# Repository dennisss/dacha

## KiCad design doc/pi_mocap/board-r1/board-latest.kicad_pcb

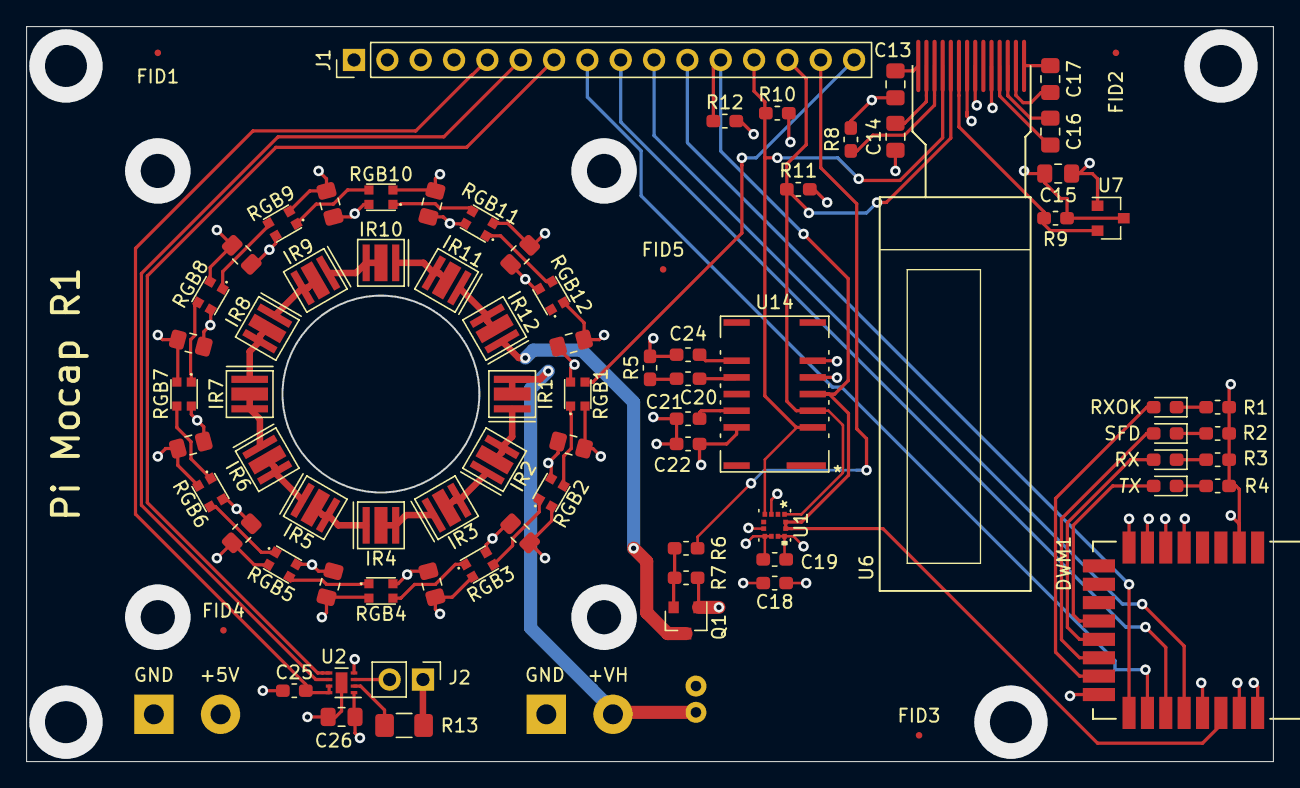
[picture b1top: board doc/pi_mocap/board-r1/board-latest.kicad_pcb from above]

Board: 4 copper layers, 95.0 x 56.0 mm, 83 parts (1 on the bottom side), 61 nets.

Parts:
C1, C2, C3, C4, C5, C6, C7, C8, C9, C10, C11, C12, C26: 0.1u; C_0805_2012Metric_Pad1.15x1.40mm_HandSolder
C13, C14, C15: 10u; C_0805_2012Metric_Pad1.15x1.40mm_HandSolder
C16, C17: 1u; C_0805_2012Metric_Pad1.15x1.40mm_HandSolder
C18, C22: 10u; C_0603_1608Metric_Pad1.05x0.95mm_HandSolder
C19: 100n; C_0603_1608Metric_Pad1.05x0.95mm_HandSolder
C20: 1u; C_0603_1608Metric_Pad1.05x0.95mm_HandSolder
C21: 1.5u; C_0603_1608Metric_Pad1.05x0.95mm_HandSolder
C23: 100u; C_Radial_D5.0mm_H11.0mm_P2.00mm
C24, C25: 0.1u; C_0603_1608Metric_Pad1.05x0.95mm_HandSolder
D1: RXOK; LED_0603_1608Metric_Pad1.05x0.95mm_HandSolder
D2: SFD; LED_0603_1608Metric_Pad1.05x0.95mm_HandSolder
D3: RX; LED_0603_1608Metric_Pad1.05x0.95mm_HandSolder
D4: TX; LED_0603_1608Metric_Pad1.05x0.95mm_HandSolder
DWM1: DWM1000
FID1, FID2, FID3, FID4, FID5: Fiducial; Fiducial_0.5mm_Mask1mm
IR1, IR2, IR3, IR4, IR5, IR6, IR7, IR8, IR9, IR10, IR11, IR12: LED; WURTH_15435385A9040
J1: AUX; PinHeader_1x16_P2.54mm_Vertical
J2: SOLENOID; PinHeader_1x02_P2.54mm_Vertical
J3: LED_DCDC_IN; TerminalBlock_bornier-2_P5.08mm
J4: LED_DCDC_OUT; TerminalBlock_bornier-2_P5.08mm
Q1: AO3422; SOT-23
R1, R2, R3, R4: 200; R_0603_1608Metric_Pad1.05x0.95mm_HandSolder
R5: 20; R_0603_1608Metric_Pad1.05x0.95mm_HandSolder
R6: 1K; R_0603_1608Metric_Pad1.05x0.95mm_HandSolder
R7, R9, R10, R11, R12: 10K; R_0603_1608Metric_Pad1.05x0.95mm_HandSolder
R8: 390K; R_0603_1608Metric_Pad1.05x0.95mm_HandSolder
R13: NC; R_1206_3216Metric_Pad1.42x1.75mm_HandSolder
RGB1, RGB2, RGB3, RGB4, RGB5, RGB6, RGB7, RGB8, RGB9, RGB10, RGB11, RGB12: WS2812B-2020
U1: LIS2DW12TR
U2: DRV8837; WSON-8-1EP_2x2mm_P0.5mm_EP0.9x1.6mm
U6: SSD1306; SSD1306_OLED-0.91-128x32
U7: APX803; SOT-23
U14: AMG8854

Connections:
+3V3: C15.2, C18.1, C19.1, C22.1, C24.1, C25.1, DWM1.5, DWM1.6, DWM1.7, J1.5, R9.2, R10.2, R11.2, R12.2, U1.9, U1.10, U2.7, U2.8, U6.5, U6.8, U7.3, U14.9, U14.13
+5V: C1.1, C2.1, C3.1, C4.1, C5.1, C6.1, C7.1, C8.1, C9.1, C10.1, C11.1, C12.1, C26.2, J1.1, J1.2, J3.2, RGB1.4, RGB2.4, RGB3.4, RGB4.4, RGB5.4, RGB6.4, RGB7.4, RGB8.4, RGB9.4, RGB10.4, RGB11.4, RGB12.4, U2.1
GND: C1.2, C2.2, C3.2, C4.2, C5.2, C6.2, C7.2, C8.2, C9.2, C10.2, C11.2, C12.2, C13.1, C14.1, C15.1, C18.2, C19.2, C21.2, C22.2, C23.2, C24.2, C25.2, C26.1, DWM1.2, DWM1.8, DWM1.16, DWM1.21, DWM1.23, DWM1.24, J1.3, J1.4, J3.1, J4.1, Q1.1, R1.2, R2.2, R3.2, R4.2, R5.2, R7.1, R8.2, RGB1.2, RGB2.2, RGB3.2, RGB4.2, RGB5.2, RGB6.2, RGB7.2, RGB8.2, RGB9.2, RGB10.2, RGB11.2, RGB12.2, U1.3, U1.6, U1.7, U1.8, U2.4, U2.9, U6.7, U7.1, U14.5, U14.6
IR_LED_PWM: J1.15, R6.1
IR_LED_VCC: C23.1, IR1.2, J4.2
LED_SERIAL: J1.16, RGB1.3
unnamed: C13.2, U6.14
unnamed: C14.2, U6.13
unnamed: C16.1, U6.4
unnamed: C16.2, U6.3
unnamed: C17.1, U6.2
unnamed: C17.2, U6.1
unnamed: C20.1, U14.10
unnamed: C20.2, R5.1
unnamed: C21.1, U14.12
unnamed: D1.1, R1.1
unnamed: D1.2, DWM1.15
unnamed: D2.1, R2.1
unnamed: D2.2, DWM1.14
unnamed: D3.1, R3.1
unnamed: D3.2, DWM1.13
unnamed: D4.1, R4.1
unnamed: D4.2, DWM1.12
unnamed: IR1.1, IR2.2
unnamed: IR2.1, IR3.2
unnamed: IR3.1, IR4.2
unnamed: IR4.1, IR5.2
unnamed: IR5.1, IR6.2
unnamed: IR6.1, IR7.2
unnamed: IR7.1, IR8.2
unnamed: IR8.1, IR9.2
unnamed: IR10.1, IR11.2
unnamed: IR9.1, IR10.2
unnamed: IR11.1, IR12.2
unnamed: IR12.1, Q1.3
unnamed: J2.1, R13.2
unnamed: J2.2, U2.3
unnamed: Q1.2, R6.2, R7.2
unnamed: R8.1, U6.12
unnamed: R13.1, U2.2
unnamed: RGB1.1, RGB2.3
unnamed: RGB2.1, RGB3.3
unnamed: RGB3.1, RGB4.3
unnamed: RGB4.1, RGB5.3
unnamed: RGB5.1, RGB6.3
unnamed: RGB6.1, RGB7.3
unnamed: RGB7.1, RGB8.3
unnamed: RGB8.1, RGB9.3
unnamed: RGB10.1, RGB11.3
unnamed: RGB9.1, RGB10.3
unnamed: RGB11.1, RGB12.3
OLED_RESET: R9.1, U6.9, U7.2
PI_I2C0_SCL: J1.14, R11.1, U1.1, U6.10, U14.3
PI_I2C0_SDA: J1.13, R10.1, U1.4, U6.11, U14.2
PI_SPI0_CE0: DWM1.17, J1.11
PI_SPI0_SCLK: DWM1.20, J1.10
PI_SPIO_MISO: DWM1.19, J1.9
PI_SPIO_MOSI: DWM1.18, J1.8
SENSOR_INTERRUPT: DWM1.22, J1.12, R12.1, U1.11, U1.12, U14.4
SOLENOID_DIR1: J1.6, U2.6
SOLENOID_DIR2: J1.7, U2.5

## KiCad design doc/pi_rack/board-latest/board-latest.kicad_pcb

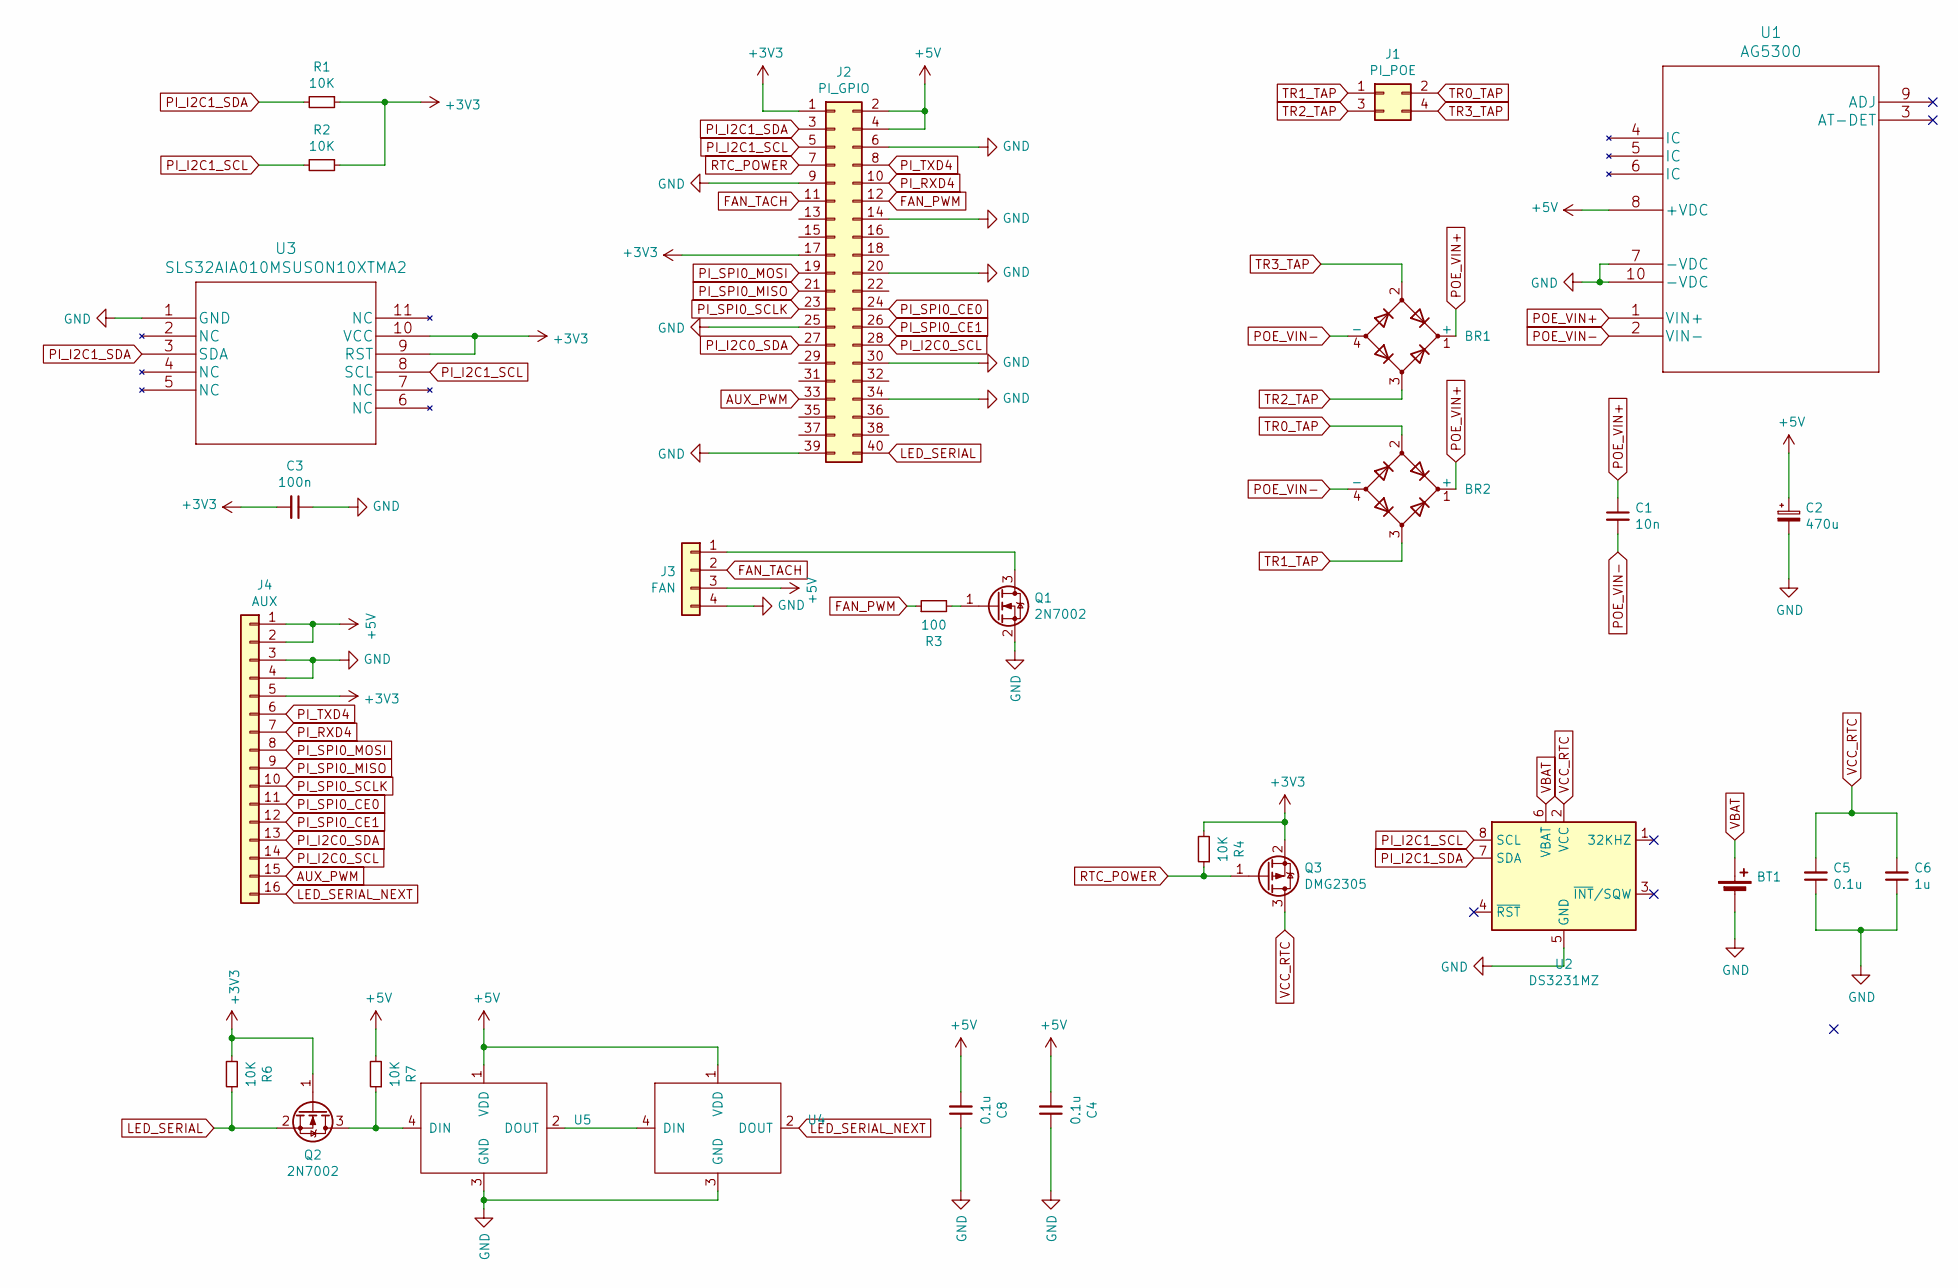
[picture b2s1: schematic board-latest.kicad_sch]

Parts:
BR1, BR2: D_Bridge_+AA-; CD-HD2004
BT1: Battery_Cell; BatteryHolder_Keystone_3000_1x12mm
C1: 10n; C_0805_2012Metric_Pad1.15x1.40mm_HandSolder
C2: 470u; CP_Radial_D10.0mm_P5.00mm
C3: 100n; C_0603_1608Metric_Pad1.05x0.95mm_HandSolder
C4, C8: 0.1u; C_0805_2012Metric_Pad1.15x1.40mm_HandSolder
C5: 0.1u; C_0603_1608Metric_Pad1.05x0.95mm_HandSolder
C6: 1u; C_0603_1608Metric_Pad1.05x0.95mm_HandSolder
J1: PI_POE; PinSocket_1x04_P2.54mm_Horizontal
J2: PI_GPIO; PinSocket_2x20_P2.54mm_Horizontal
J3: FAN; JST_SH_SM04B-SRSS-TB_1x04-1MP_P1.00mm_Horizontal
J4: AUX; Harwin_M20-89016xx_1x16_P2.54mm_Horizontal
Q1, Q2: 2N7002; SOT-23
Q3: DMG2305; SOT-23
R1, R2, R4, R6, R7: 10K; R_0603_1608Metric_Pad1.05x0.95mm_HandSolder
R3: 100; R_0603_1608Metric_Pad1.05x0.95mm_HandSolder
U1: AG5300; AG5400
U2: DS3231MZ; SOIC-8_3.9x4.9mm_P1.27mm
U3: SLS32AIA010MSUSON10XTMA2
U4, U5: SK6812MINI-E; SK6812B-SIDE

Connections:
+3V3: C3.2, J2.1, J2.17, J4.5, Q2.1 (G), Q3.2 (S), R1.1, R2.1, R4.2, R6.2, U3.9 (RST), U3.10 (VCC)
+5V: C2.1, C4.2, C8.2, J2.2, J2.4, J3.3, J4.1, J4.2, R7.2, U1.8 (+VDC), U4.1 (VDD), U5.1 (VDD)
AUX_PWM: J2.33, J4.15
FAN_PWM: J2.12, R3.1
FAN_TACH: J2.11, J3.2
GND: BT1.2 (-), C2.2, C3.1, C4.1, C5.1, C6.1, C8.1, J2.6, J2.9, J2.14, J2.20, J2.25, J2.30, J2.34, J2.39, J3.4, J4.3, J4.4, Q1.2 (S), U1.7 (-VDC), U1.10 (-VDC), U2.5 (GND), U3.1 (GND), U4.3 (GND), U5.3 (GND)
LED_SERIAL: J2.40, Q2.2 (S), R6.1
LED_SERIAL_NEXT: J4.16, U4.2 (DOUT)
unnamed: J3.1, Q1.3 (D)
unnamed: Q1.1 (G), R3.2
unnamed: Q2.3 (D), R7.1, U5.4 (DIN)
unnamed: U4.4 (DIN), U5.2 (DOUT)
PI_I2C0_SCL: J2.28, J4.14
PI_I2C0_SDA: J2.27, J4.13
PI_I2C1_SCL: J2.5, R2.2, U2.8 (SCL), U3.8 (SCL)
PI_I2C1_SDA: J2.3, R1.2, U2.7 (SDA), U3.3 (SDA)
PI_RXD4: J2.10, J4.7
PI_SPI0_CE0: J2.24, J4.11
PI_SPI0_CE1: J2.26, J4.12
PI_SPI0_MISO: J2.21, J4.9
PI_SPI0_MOSI: J2.19, J4.8
PI_SPI0_SCLK: J2.23, J4.10
PI_TXD4: J2.8, J4.6
POE_VIN+: BR1.1 (+), BR2.1 (+), C1.1, U1.1 (VIN+)
POE_VIN-: BR1.4 (-), BR2.4 (-), C1.2, U1.2 (VIN-)
RTC_POWER: J2.7, Q3.1 (G), R4.1
TR0_TAP: BR2.2, J1.2
TR1_TAP: BR2.3, J1.1
TR2_TAP: BR1.3, J1.3
TR3_TAP: BR1.2, J1.4
VBAT: BT1.1 (+), U2.6 (VBAT)
VCC_RTC: C5.2, C6.2, Q3.3 (D), U2.2 (VCC)

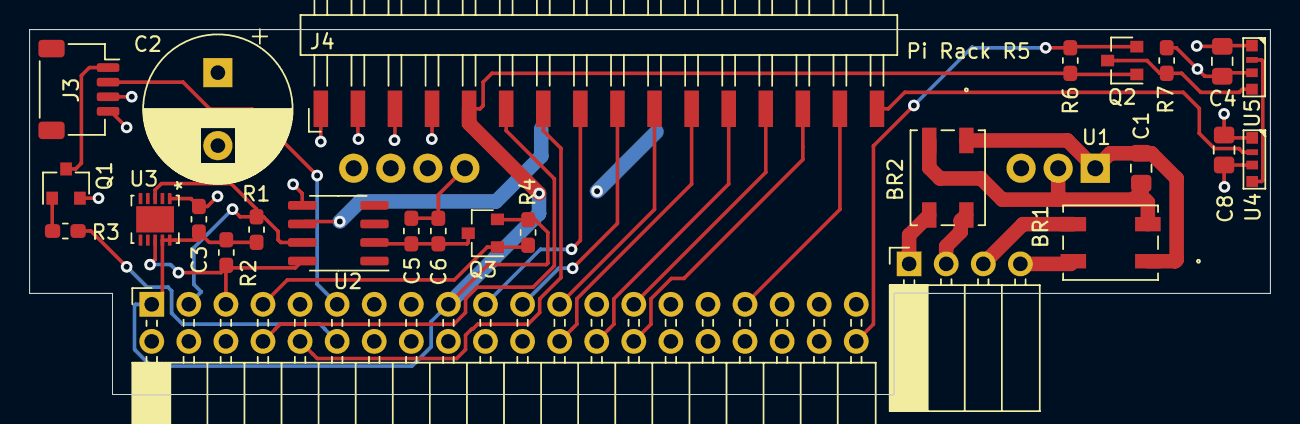
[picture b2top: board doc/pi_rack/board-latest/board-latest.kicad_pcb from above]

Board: 4 copper layers, 85.0 x 25.0 mm, 28 parts (1 on the bottom side), 32 nets.

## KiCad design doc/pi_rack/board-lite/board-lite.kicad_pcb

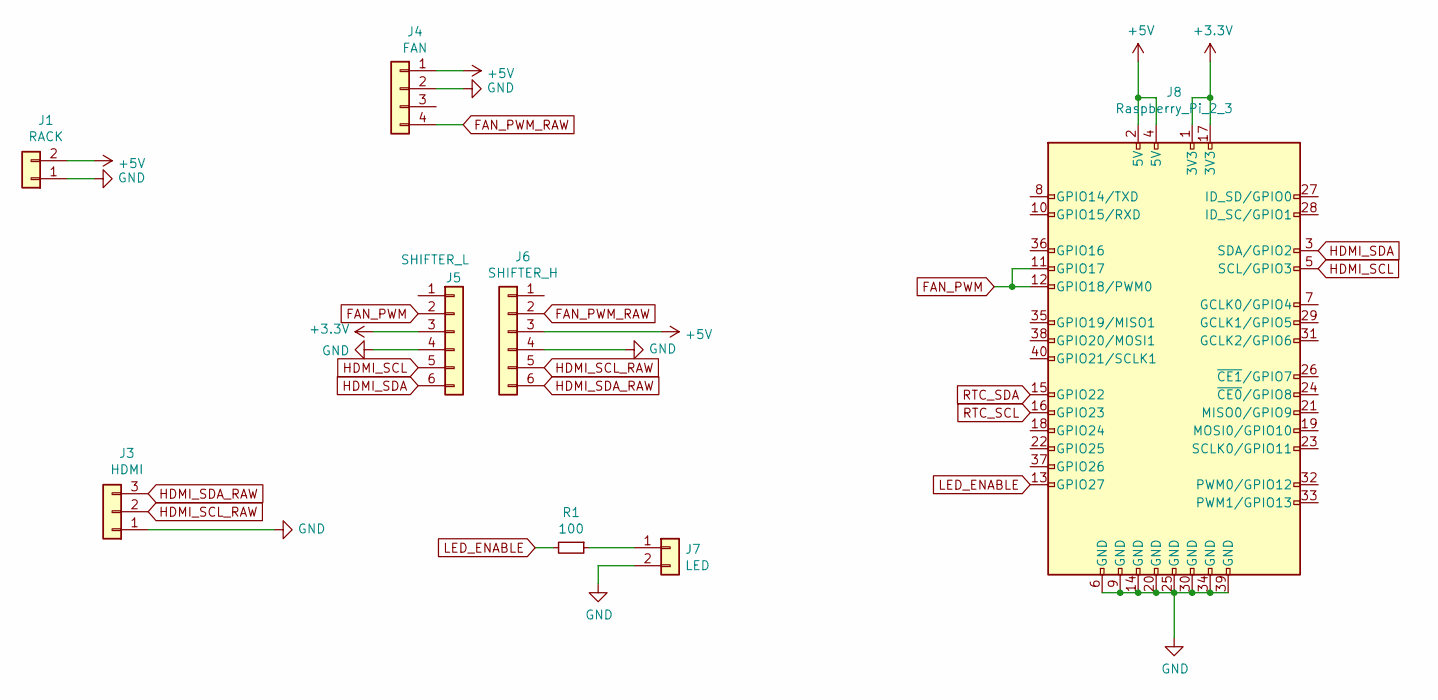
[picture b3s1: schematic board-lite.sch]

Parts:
J1: RACK; PinHeader_1x02_P2.54mm_Horizontal
J3: HDMI; PinHeader_1x03_P2.54mm_Horizontal
J4: FAN; PinHeader_1x04_P2.54mm_Horizontal
J5: SHIFTER_L; PinHeader_1x06_P2.54mm_Vertical
J6: SHIFTER_H; PinHeader_1x06_P2.54mm_Vertical
J7: LED; PinHeader_1x02_P2.54mm_Horizontal
J8: Raspberry_Pi_2_3; PinHeader_2x20_P2.54mm_Vertical
R1: 100; R_0805_2012Metric_Pad1.15x1.40mm_HandSolder

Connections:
+3V3: J5.3, J8.1 (3V3), J8.17 (3V3)
+5V: J1.2, J4.1, J6.3, J8.2 (5V), J8.4 (5V)
FAN_PWM: J5.2, J8.11 (GPIO17), J8.12 (GPIO18/PWM0)
FAN_PWM_RAW: J4.4, J6.2
GND: J1.1, J3.1, J4.2, J5.4, J6.4, J7.2, J8.6 (GND), J8.9 (GND), J8.14 (GND), J8.20 (GND), J8.25 (GND), J8.30 (GND), J8.34 (GND), J8.39 (GND)
HDMI_SCL: J5.5, J8.5 (SCL/GPIO3)
HDMI_SCL_RAW: J3.2, J6.5
HDMI_SDA: J5.6, J8.3 (SDA/GPIO2)
HDMI_SDA_RAW: J3.3, J6.6
LED_ENABLE: J8.13 (GPIO27), R1.2
unnamed: J7.1, R1.1
RTC_SCL: J8.16 (GPIO23)
RTC_SDA: J8.15 (GPIO22)

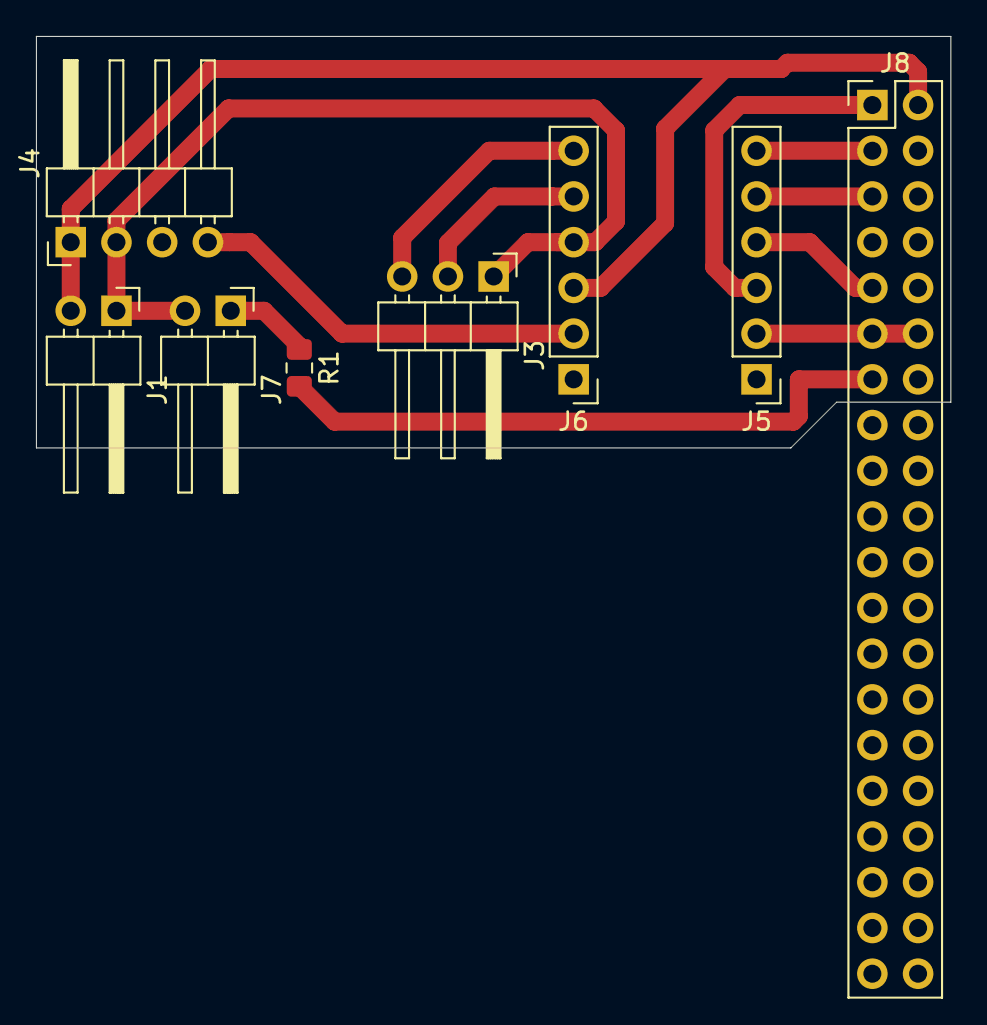
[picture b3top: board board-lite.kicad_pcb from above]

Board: 2 copper layers, 50.8 x 22.9 mm, 8 parts (0 on the bottom side), 11 nets.

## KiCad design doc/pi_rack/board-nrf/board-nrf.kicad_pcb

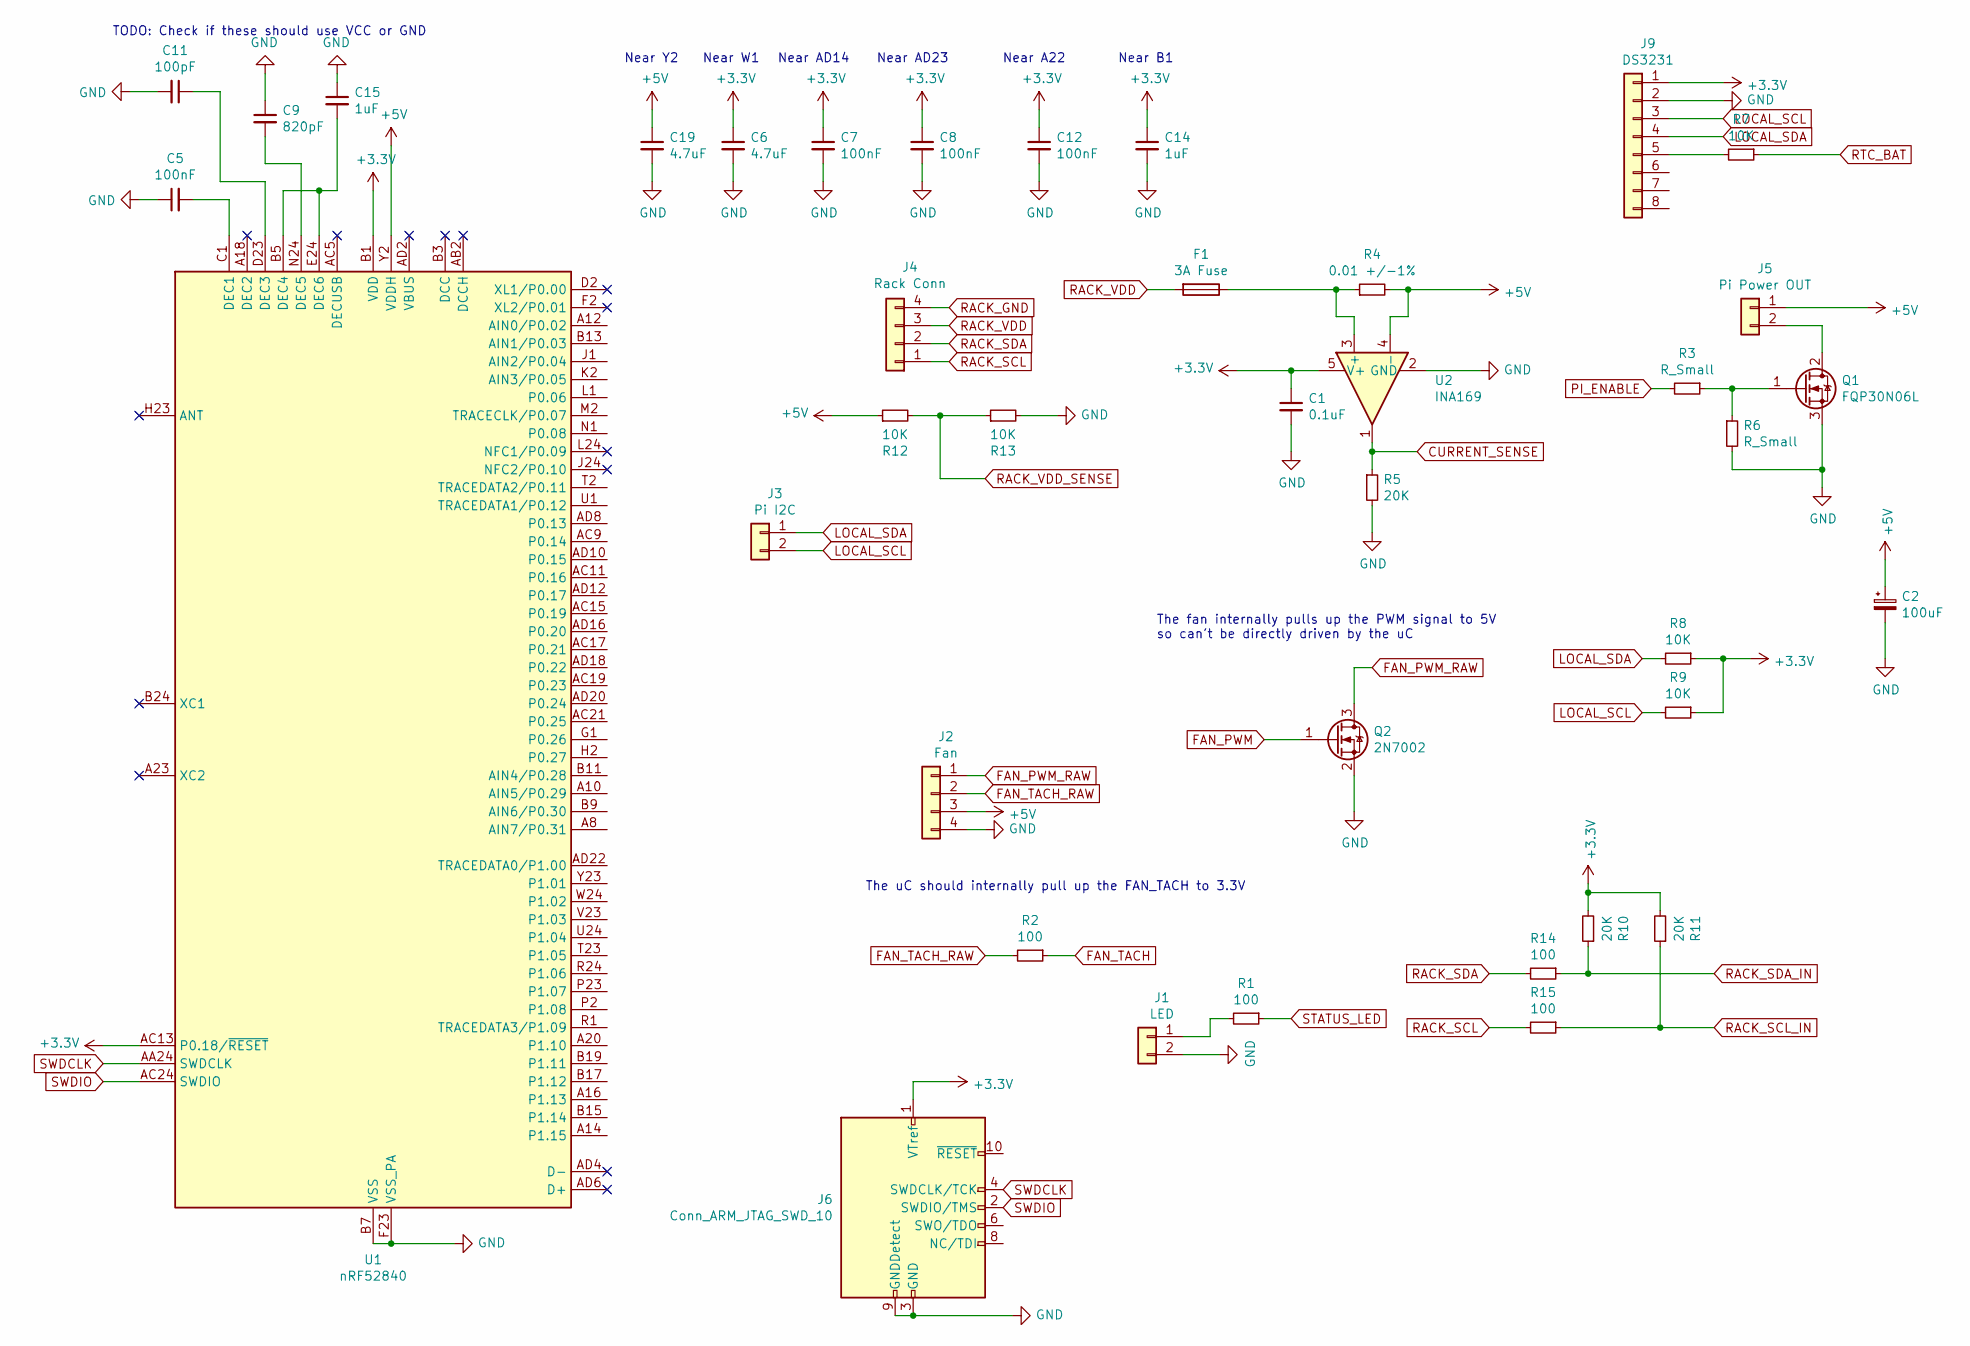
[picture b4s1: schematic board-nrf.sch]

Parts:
C1: 0.1uF; C_0603_1608Metric
C2: 100uF; CP_Radial_D5.0mm_P2.50mm
C5, C7, C8, C12: 100nF; C_0402_1005Metric
C6, C19: 4.7uF; C_0603_1608Metric
C9: 820pF; C_0402_1005Metric
C11: 100pF; C_0402_1005Metric
C14, C15: 1uF; C_0603_1608Metric
F1: 3A Fuse; FC-203-22
J1: LED; PinHeader_2x01_P2.54mm_Vertical
J2: Fan; PinHeader_1x04_P2.54mm_Vertical
J3: Pi I2C; PinHeader_2x01_P2.54mm_Vertical
J4: Rack Conn; JST_XH_B4B-XH-A_1x04_P2.50mm_Vertical
J5: Pi Power OUT; PinHeader_2x01_P2.54mm_Vertical
J6: Conn_ARM_JTAG_SWD_10; PinHeader_2x05_P1.27mm_Vertical
J9: DS3231; PinHeader_1x08_P2.54mm_Vertical
Q1: FQP30N06L; TO-220-3_Vertical
Q2: 2N7002; SOT-23
R1, R2: 100; R_0805_2012Metric_Pad1.15x1.40mm_HandSolder
R3, R6: R_Small; R_0603_1608Metric
R4: 0.01 +/-1%; R_0805_2012Metric_Pad1.15x1.40mm_HandSolder
R5: 20K; R_0201_0603Metric
R7, R8, R9, R12, R13: 10K; R_0603_1608Metric
R10, R11: 20K; R_0603_1608Metric
R14, R15: 100; R_0603_1608Metric
U1: nRF52840; Nordic_AQFN-73-1EP_7x7mm_P0.5mm
U2: INA169; SOT-23-5

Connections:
+3V3: C1.1, C6.1, C7.1, C8.1, C12.1, C14.1, J6.1 (VTref), J9.1, R8.1, R9.1, R10.2, R11.2, U1.A22 (VDD), U1.AC13 (P0.18/~RESET), U1.AD14 (VDD), U1.AD23 (VDD), U1.B1 (VDD), U1.W1 (VDD), U2.5 (V+)
CURRENT_SENSE: R5.1, U2.1
FAN_PWM: Q2.1 (G)
FAN_PWM_RAW: J2.1, Q2.3 (D)
FAN_TACH: R2.1
FAN_TACH_RAW: J2.2, R2.2
GND: C1.2, C2.2, C5.1, C6.2, C7.2, C8.2, C9.1, C11.2, C12.2, C14.2, C15.1, C19.2, J1.2, J2.4, J6.3 (GND), J6.5 (GND), J6.9 (GNDDetect), J9.2, Q1.3 (S), Q2.2 (S), R5.2, R6.2, R13.2, U1.B7 (VSS), U1.EP (VSS), U1.F23 (VSS_PA), U2.2 (GND)
LOCAL_SCL: J3.2, J9.3, R9.2
LOCAL_SDA: J3.1, J9.4, R8.2
unnamed: C5.2, U1.C1 (DEC1)
unnamed: C9.2, U1.N24 (DEC5)
unnamed: C11.1, U1.D23 (DEC3)
unnamed: C15.2, U1.B5 (DEC4), U1.E24 (DEC6)
unnamed: F1.1, R4.1, U2.3 (+)
unnamed: J1.1, R1.2
unnamed: J5.2, Q1.2 (D)
unnamed: J9.5, R7.2
unnamed: Q1.1 (G), R3.1, R6.1
PI_ENABLE: R3.2
RACK_GND: J4.4
RACK_SCL: J4.1, R15.2
RACK_SCL_IN: R11.1, R15.1
RACK_SDA: J4.2, R14.2
RACK_SDA_IN: R10.1, R14.1
RACK_VDD_SENSE: R12.2, R13.1
RTC_BAT: R7.1
STATUS_LED: R1.1
SWDCLK: J6.4 (SWDCLK/TCK), U1.AA24 (SWDCLK)
SWDIO: J6.2 (SWDIO/TMS), U1.AC24 (SWDIO)

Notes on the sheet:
Near W1
Near Y2
Near AD14
Near AD23
Near A22
Near B1
The fan internally pulls up the PWM signal to 5V so can't be directly driven by the uC
The uC should internally pull up the FAN_TACH to 3.3V
TODO: Check if these should use VCC or GND

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
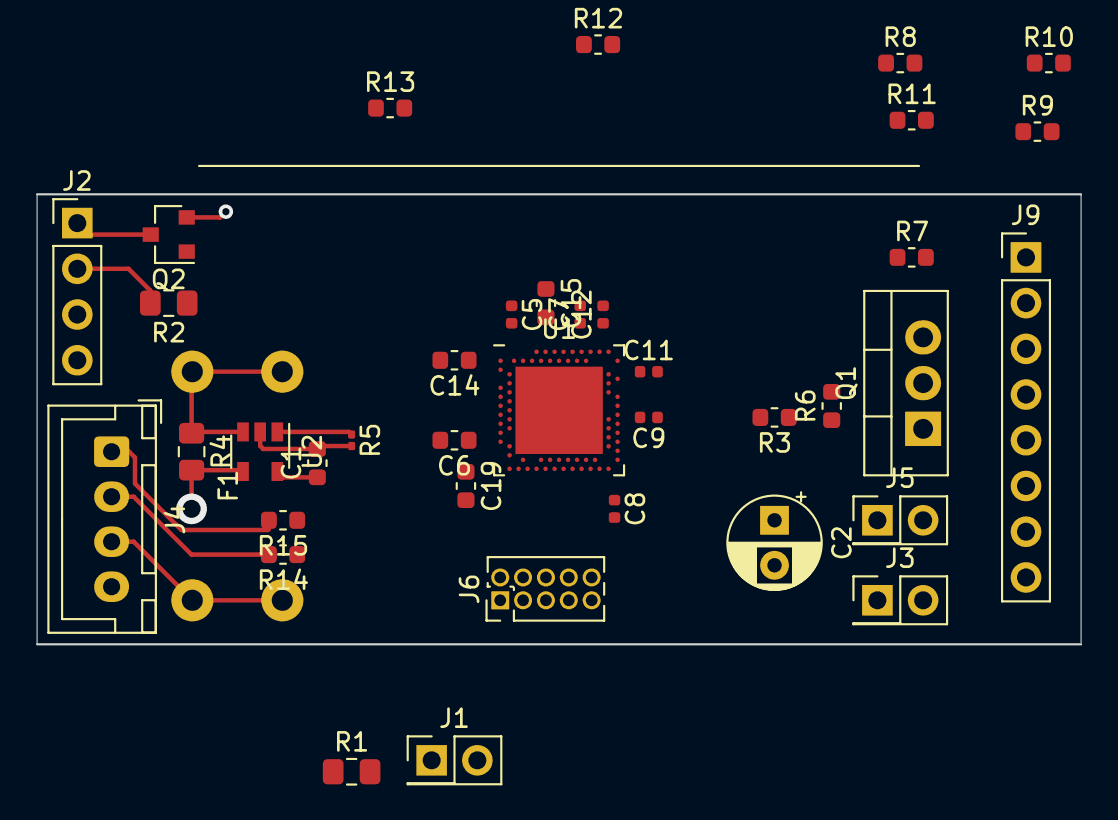
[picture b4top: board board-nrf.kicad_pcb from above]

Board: 2 copper layers, 58.0 x 25.0 mm, 39 parts (0 on the bottom side), 25 nets.

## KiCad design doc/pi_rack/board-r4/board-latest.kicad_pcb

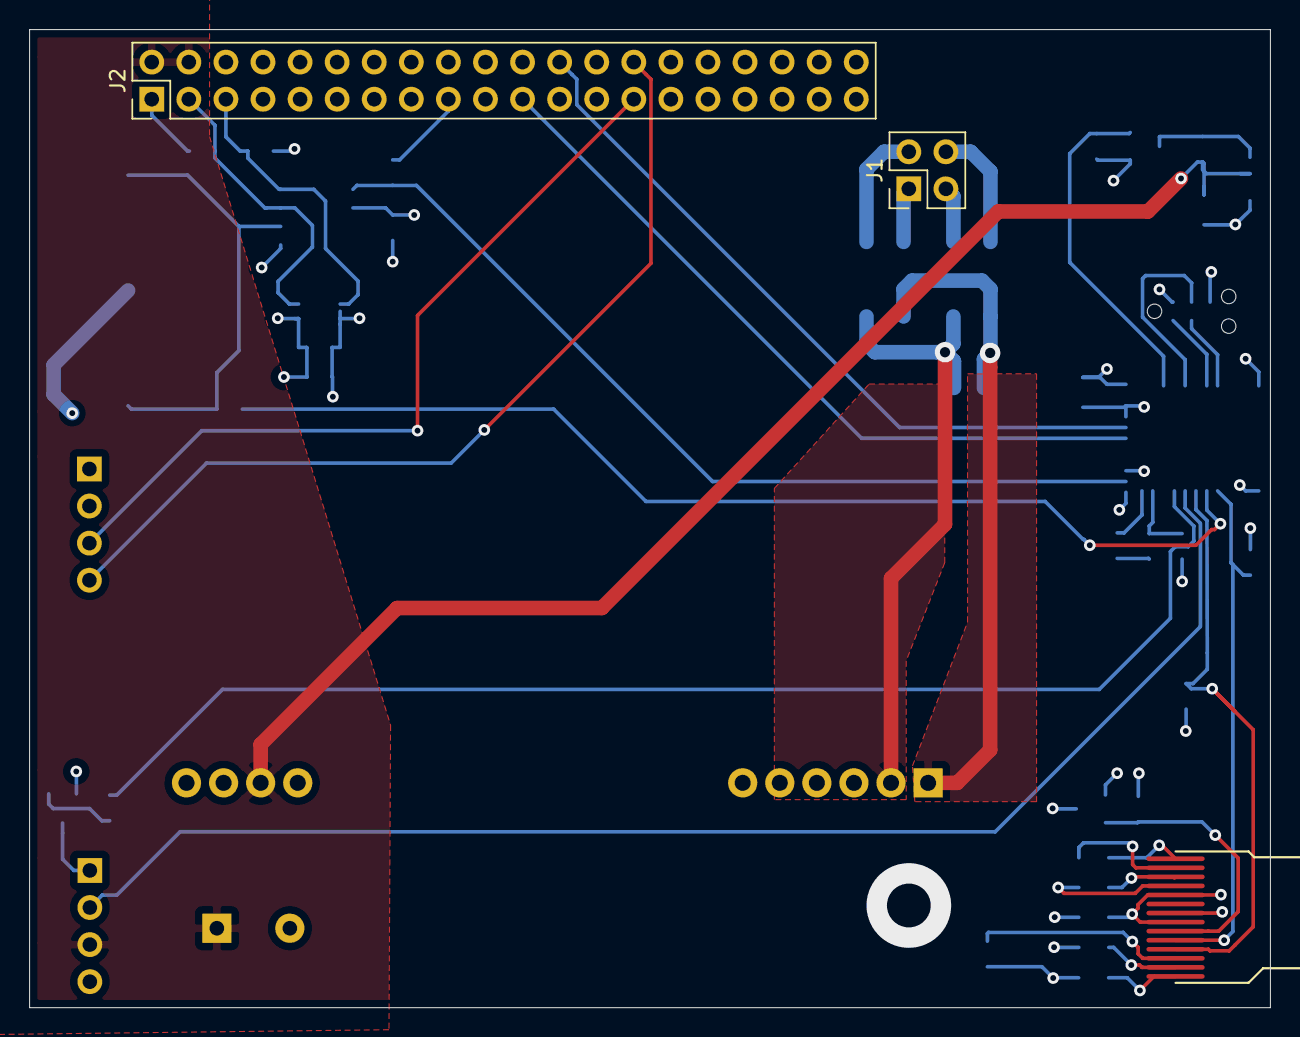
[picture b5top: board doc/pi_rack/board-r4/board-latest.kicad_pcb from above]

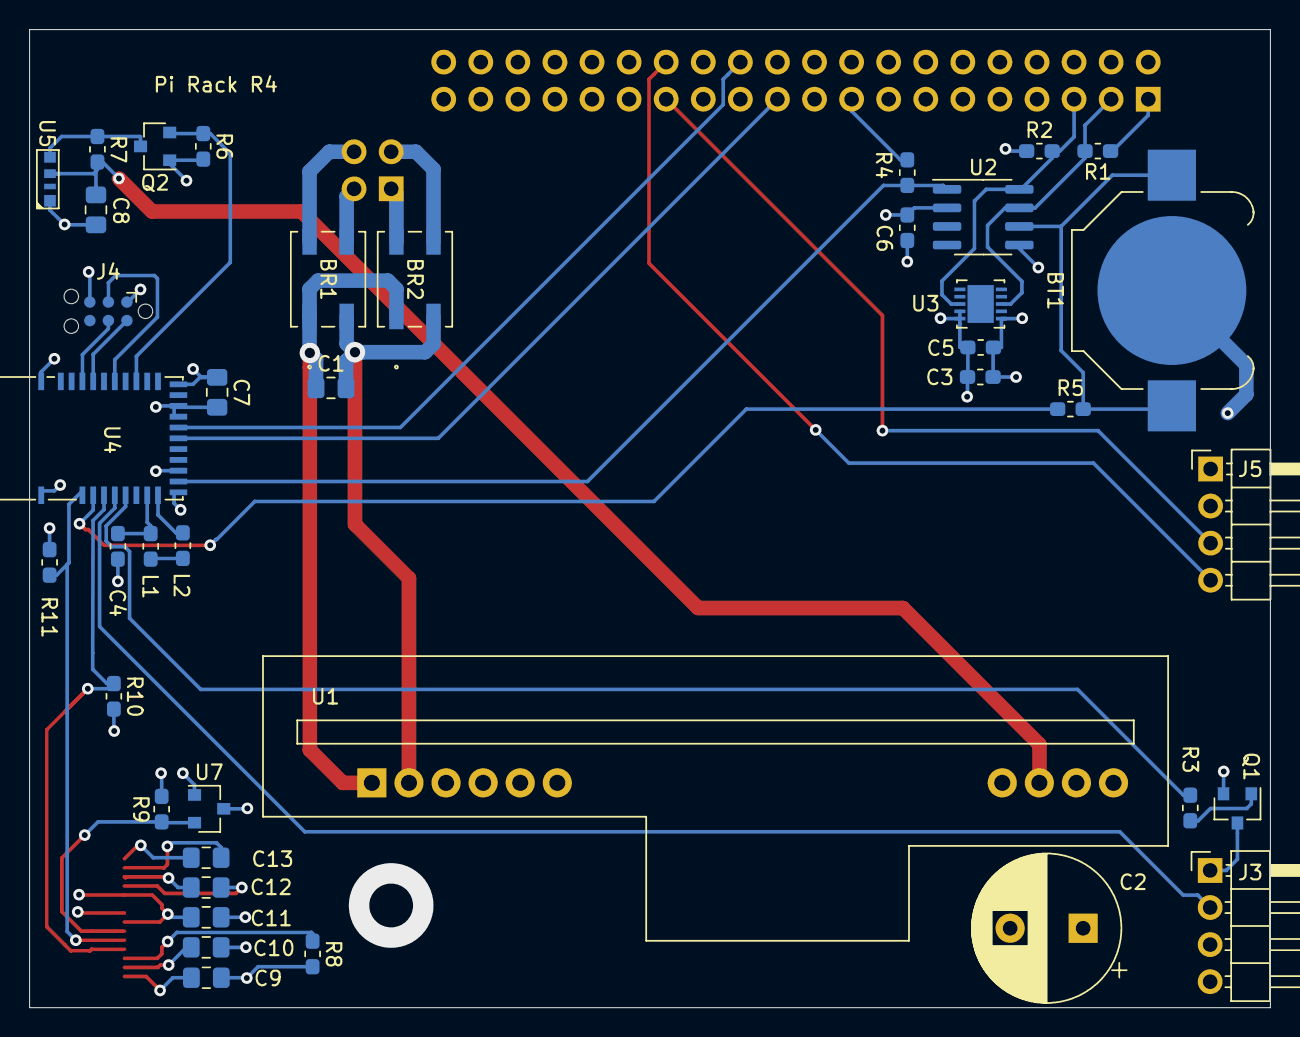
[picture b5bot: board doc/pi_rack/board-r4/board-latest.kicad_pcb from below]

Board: 4 copper layers, 85.0 x 67.0 mm, 43 parts (40 on the bottom side), 40 nets.

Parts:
BR1, BR2: D_Bridge_+AA-; CD-HD2004
BT1: Battery_Cell; BatteryHolder_Keystone_3000_1x12mm
C1: 10n; C_0805_2012Metric_Pad1.15x1.40mm_HandSolder
C2: 470u; CP_Radial_D10.0mm_P5.00mm
C3: 100n; C_0603_1608Metric_Pad1.05x0.95mm_HandSolder
C4, C6: 1u; C_0603_1608Metric_Pad1.05x0.95mm_HandSolder
C5: 0.1u; C_0603_1608Metric_Pad1.05x0.95mm_HandSolder
C7, C9, C10, C11: 10u; C_0805_2012Metric_Pad1.15x1.40mm_HandSolder
C8: 0.1u; C_0805_2012Metric_Pad1.15x1.40mm_HandSolder
C12, C13: 1u; C_0805_2012Metric_Pad1.15x1.40mm_HandSolder
J1: PI_POE; PinHeader_2x02_P2.54mm_Vertical
J2: PI_GPIO; PinHeader_2x20_P2.54mm_Vertical
J3: FAN; PinHeader_1x04_P2.54mm_Horizontal
J4: Conn_02x03_Odd_Even; Tag-Connect_TC2030-IDC-NL_2x03_P1.27mm_Vertical
J5: AUX; PinHeader_1x04_P2.54mm_Horizontal
L1: 15n; C_0603_1608Metric_Pad1.05x0.95mm_HandSolder
L2: 10u; C_0603_1608Metric_Pad1.05x0.95mm_HandSolder
Q1, Q2: 2N7002; SOT-23
R1, R2, R4, R6, R7, R9, R10, R11: 10K; R_0603_1608Metric_Pad1.05x0.95mm_HandSolder
R3: 100; R_0603_1608Metric_Pad1.05x0.95mm_HandSolder
R5: 100K; R_0603_1608Metric_Pad1.05x0.95mm_HandSolder
R8: 390K; R_0603_1608Metric_Pad1.05x0.95mm_HandSolder
U1: AG5300; AG5400
U2: DS3231MZ; SOIC-8_3.9x4.9mm_P1.27mm
U3: SLS32AIA010MSUSON10XTMA2
U4: MDBT50-512K
U5: SK6812MINI-E; SK6812B-SIDE
U6: SSD1306; SSD1306_OLED-0.91-128x32
U7: APX803; SOT-23

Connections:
+3V3: C3.2, C5.2, C6.2, C7.2, C11.2, J2.1, J2.17, J4.1, J5.2, Q2.1, R1.1, R2.1, R4.2, R6.2, R9.2, R10.2, R11.2, U2.2, U3.9, U3.10, U4.17, U4.18, U6.5, U6.8, U7.3
+5V: C2.1, C8.2, J2.2, J2.4, J3.3, R7.2, U1.8, U5.1
FAN_PWM: R3.1, U4.6
FAN_TACH: J3.2, U4.5
GND: BT1.2, C2.2, C3.1, C4.2, C5.1, C6.1, C7.1, C8.1, C9.1, C10.1, C11.1, J2.6, J2.9, J2.14, J2.20, J2.25, J2.30, J2.34, J2.39, J3.4, J4.5, J5.1, Q1.2, R8.2, U1.7, U1.10, U2.5, U3.1, U4.1, U4.10, U4.12, U4.20, U4.31, U5.3, U6.7, U7.1
LED_SERIAL: Q2.2, R6.1, U4.23
unnamed: C4.1, L1.1, U4.8
unnamed: C9.2, U6.14
unnamed: C10.2, U6.13
unnamed: C12.1, U6.4
unnamed: C12.2, U6.3
unnamed: C13.1, U6.2
unnamed: C13.2, U6.1
unnamed: J3.1, Q1.3
unnamed: L1.2, L2.1
unnamed: L2.2, U4.9
unnamed: Q1.1, R3.2
unnamed: Q2.3, R7.1, U5.4
unnamed: R8.1, U6.12
OLED_RESET: R9.1, U6.9, U7.2
OLED_SCL: R11.1, U4.2, U6.10
OLED_SDA: R10.1, U4.4, U6.11
PI_I2C0_SCL: J2.28, J5.4
PI_I2C0_SDA: J2.27, J5.3
PI_I2C1_SCL: J2.5, R2.2, U2.8, U3.8
PI_I2C1_SDA: J2.3, R1.2, U2.7, U3.3
PI_RXD4: J2.21, U4.15
PI_TXD4: J2.24, U4.16
POE_VIN+: BR1.1, BR2.1, C1.1, U1.1
POE_VIN-: BR1.4, BR2.4, C1.2, U1.2
RESET: J4.3, U4.25
RTC_CLK: R4.1, U2.1, U4.11
SWDCLK: J4.4, U4.28
SWDIO: J4.2, U4.27
TR0_TAP: BR2.3, J1.2
TR1_TAP: BR2.2, J1.1
TR2_TAP: BR1.2, J1.4
TR3_TAP: BR1.3, J1.3
VBAT: BT1.1, R5.2, U2.6
VBAT_MEASURE: R5.1, U4.3

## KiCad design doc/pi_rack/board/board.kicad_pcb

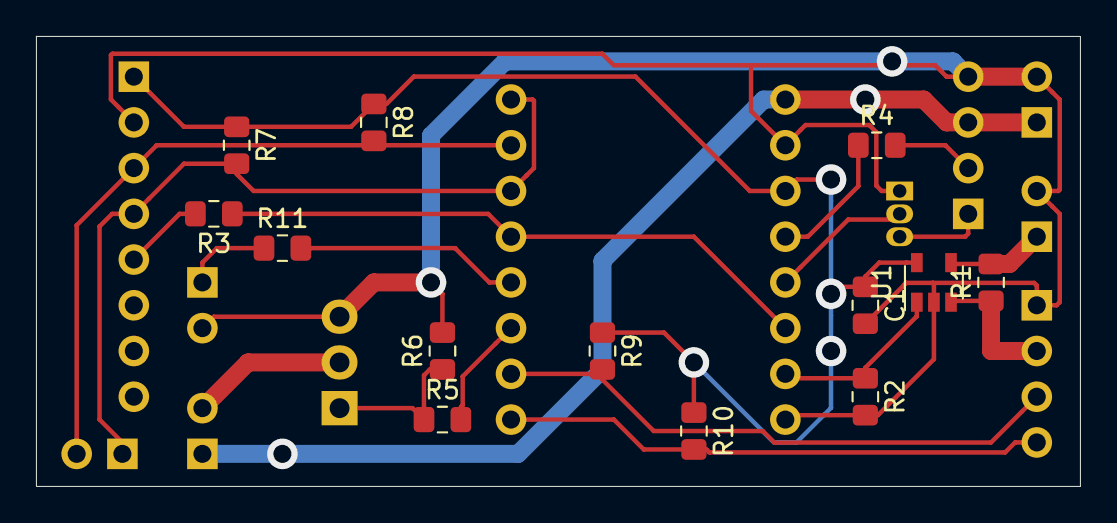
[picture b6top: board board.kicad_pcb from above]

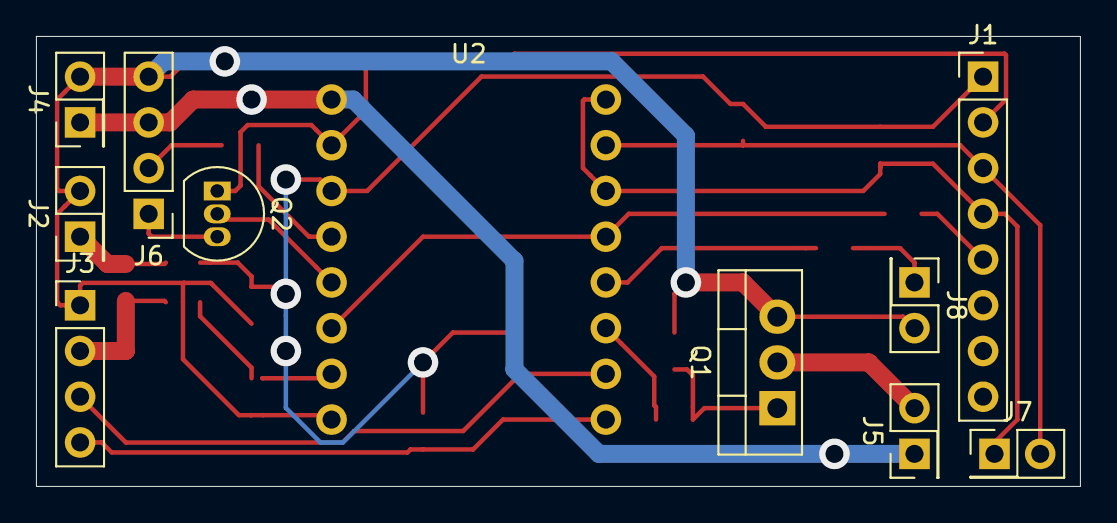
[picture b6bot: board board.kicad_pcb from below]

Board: 2 copper layers, 58.0 x 25.0 mm, 24 parts (11 on the bottom side), 21 nets.

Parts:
C1: 0.1uF; C_0805_2012Metric_Pad1.15x1.40mm_HandSolder
J1: DS3231; PinHeader_1x08_P2.54mm_Vertical
J2: Power DC/DC IN; PinHeader_2x01_P2.54mm_Vertical
J3: Rack Conn; PinHeader_1x04_P2.54mm_Vertical
J4: Power DC/DC OUT; PinHeader_2x01_P2.54mm_Vertical
J5: Pi Power OUT; PinHeader_2x01_P2.54mm_Vertical
J6: Fan; PinHeader_1x04_P2.54mm_Vertical
J7: Pi I2C; PinHeader_2x01_P2.54mm_Vertical
J8: LED; PinHeader_2x01_P2.54mm_Vertical
Q1: FQP30N06L; TO-220-3_Vertical
Q2: 2N7000; TO-92_Inline
R1: 0.1 +/-1%; R_0805_2012Metric_Pad1.15x1.40mm_HandSolder
R2, R5, R6: R_Small; R_0805_2012Metric_Pad1.15x1.40mm_HandSolder
R3, R7, R8: 10K; R_0805_2012Metric_Pad1.15x1.40mm_HandSolder
R4, R11: 100; R_0805_2012Metric_Pad1.15x1.40mm_HandSolder
R9, R10: 20K; R_0805_2012Metric_Pad1.15x1.40mm_HandSolder
U1: INA169; SOT-23-5
U2: TINY2040; TINY2040_TH

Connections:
+3V3: C1.1, J1.1, R7.1, R8.1, R9.1, R10.1, U1.5, U2.3
+5V: J4.1, J5.1, J6.3, U2.1
+24V: J2.1, R1.2, U1.4
CURRENT_SENSE: R2.1, U1.1, U2.7
FAN_PWM: Q2.2, U2.5
FAN_PWM_RAW: J6.1, Q2.3
FAN_TACH: R4.1, U2.4
FAN_TACH_RAW: J6.2, R4.2
GND: C1.2, J1.2, J2.2, J3.1, J4.2, J6.4, J8.2, Q1.3, Q2.1, R2.2, R6.2, U1.2, U2.2, U2.8
LOCAL_SCL: J1.3, J7.2, R8.2, U2.15
LOCAL_SDA: J1.4, J7.1, R7.2, U2.14, U2.16
unnamed: J1.5, R3.2
unnamed: J5.2, Q1.2
unnamed: J8.1, R11.1
unnamed: Q1.1, R5.1, R6.1
PI_ENABLE: R5.2, U2.11
RACK_SCL: J3.4, R10.2, U2.9
RACK_SDA: J3.3, R9.2, U2.10
RACK_VDD: J3.2, R1.1, U1.3
RTC_BAT: R3.1, U2.6, U2.13
STATUS_LED: R11.2, U2.12

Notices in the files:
parts and their libraries:
Copyright 2021 Accelerated Designs. All rights reserved.
